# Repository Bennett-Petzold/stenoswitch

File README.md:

Split stenography keyboard supporting USB, Bluetooth, battery, and embedded Plover translation.

# Warning!!!
There is no warranty, implied or otherwise, on this repository!
This is a hobby project by someone who has no formal education or training in PCB design. 
I _CANNOT_ guarantee that the battery circuit is safe.
I _CANNOT_ guarantee bluetooth communications comply with safety regulations.
I _AM NOT_ liable if you make this project and it is dysfunctional.
Understand that there is a risk of electrical fire due to the lithium ion battery.
Understand that wireless communications are untested and may interfere with pacemakers etc.

# Capabilities
TODO.

# Licenses
All code is licensed under the Mozilla Public License 2.0.
All non-code is licensed under CC BY-SA 4.0.
Both licenses allow for commercial use, but any commercial modification must be licensed under the same terms.
They will not "infect" other proprietary works.

# Subfolders
Each subfolder 

## Assembling the Project
See [assembly/README.md](assembly/README.md).

## PCB
KiCAD designs for printed circuit board.
See [pcb/README.md](pcb/README.md) for more.

## Software
Hardware-independent software built into the machine image.
Specialization to a specific hardware is handled in yocto.
See [software/README.md](software/README.md).

## Yocto Image
This defines the machine-specific image.
See [yocto/README.md](yocto/README.md).

# Releases
Some release resources are manually uploaded.
The initial install is done with the full disk image.
Subsequent updates are done by flashing ONLY the length of the full disk image.

# Appendix

### Steno Resources
* https://www.openstenoproject.org/plover/
* https://plover.wiki/index.php/Plover_Wiki
* https://lapwing.aerick.ca/
* https://www.artofchording.com/
* https://www.openstenoproject.org/learn-plover/home.html

### Approximate Cost
These are based on my costs (including shipping and taxes) September 2025, US address.
* $35 for keyswitches and lube
* $18 for springs
* $12 for battery
* $17 for Raspberry Pi
* $60 for components from DigiKey
* $50 for 5 PCBs both sides, 1 stencil from JLCPCB
Expect ~ $200 for a full single order.
There are electronics and buying in bulk reduces per-board prices.
Shipping is also a significant part of the price in these low quantities.

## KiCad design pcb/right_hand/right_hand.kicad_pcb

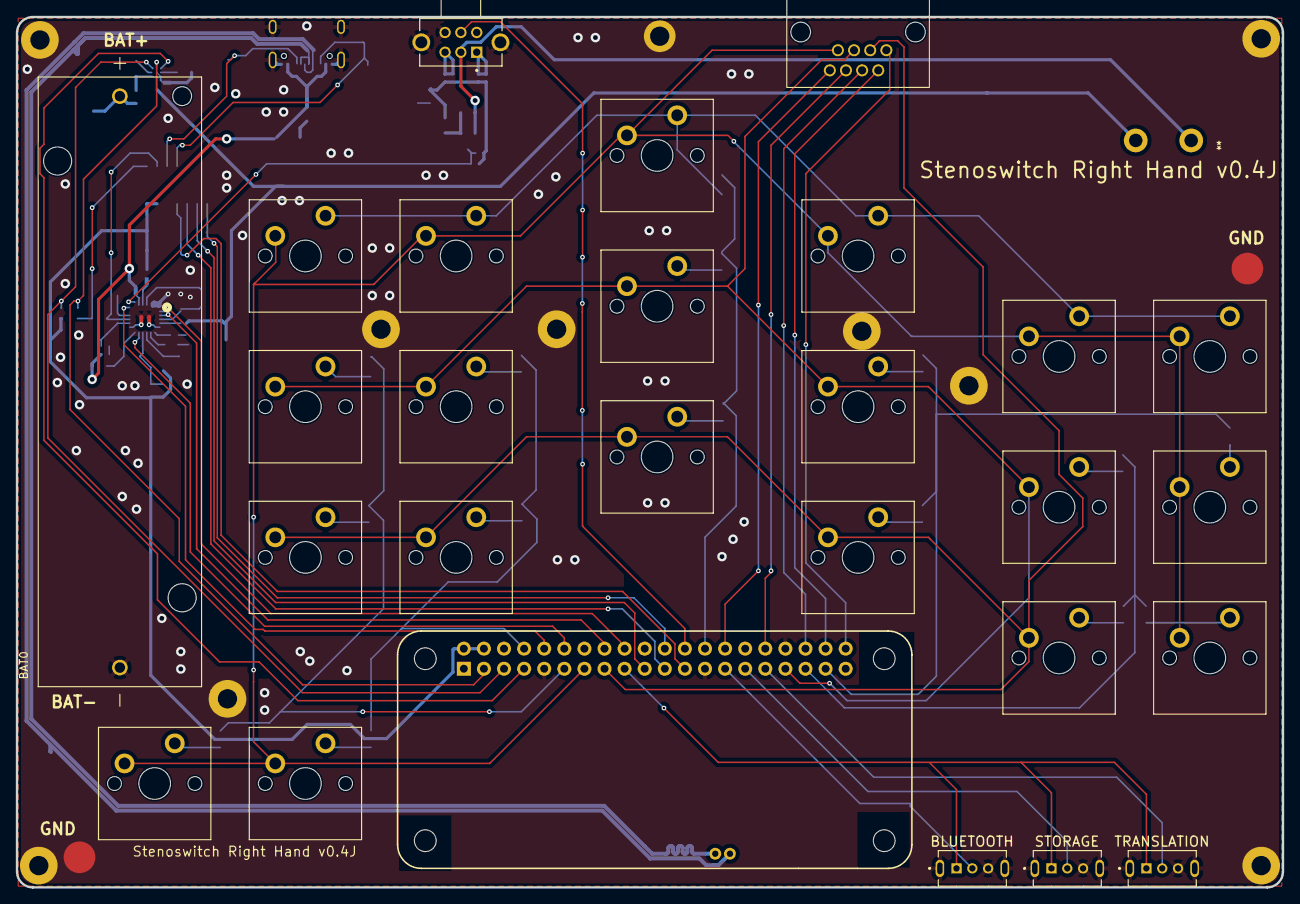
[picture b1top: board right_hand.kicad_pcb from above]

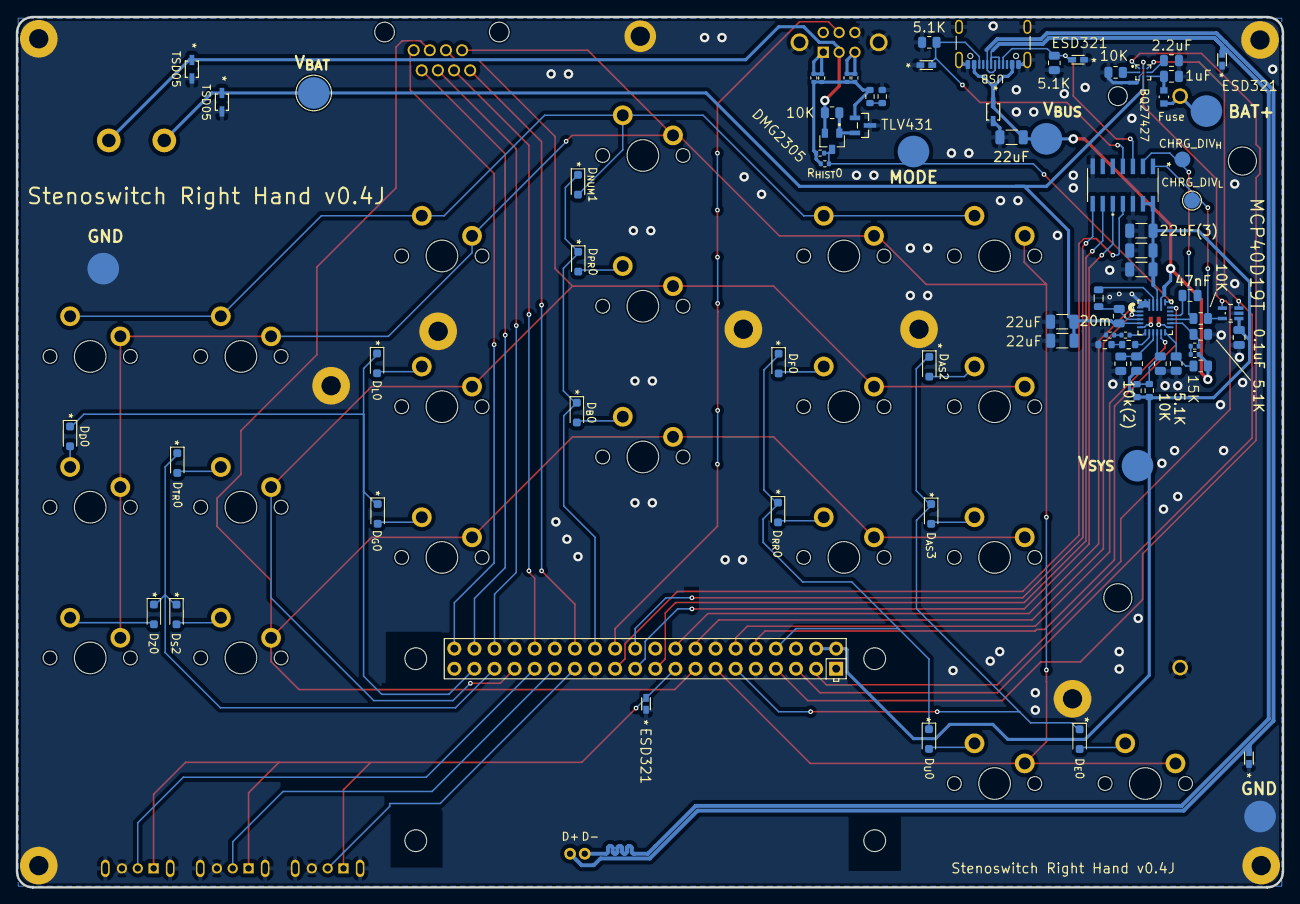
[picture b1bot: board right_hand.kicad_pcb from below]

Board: 2 copper layers, 160.0 x 110.0 mm, 104 parts (75 on the bottom side), 82 nets.

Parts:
A1: Raspberry Pi Zero v1.3; RASPI_ZERO_FULL
Asterisk2, Asterisk3: SW_Push; SW_Cherry_MX_PCB
B0: SW_Push; SW_Cherry_MX_PCB
BAT0: 1043; BAT_1043
BAT_Decouple0: 1uF; C_0805_2012Metric
BAT_EN0: RA1H1C112R; SW_RA1H1C112R_EWI
BAT_Fuse0: 2.5 A; FUSE_ERBRE_PAN
BAT_MIN0: DMG2305UX-7; SOT91P240X110-3N_DMG2305UX-7
BIN_Pulldown0: 10K; R_0805_2012Metric
BLUETOOTH0: SLW-864587-2A-RA-N-D; SW_SLW-864587-2A-RA-N-D
Battery_Charger0: MP2637GR-P; QFN-24_MP2637_MNP
Battery_Monitor0: BQ27427YZFR; IC_BQ27427YZFR
CHRG_Bypass0: 2.2uH; L_0805_2012Metric
CHRG_DIV_{L}: TestPoint_Pad_D2.0mm
CHRG_Decouple0: 47nF; C_0805_2012Metric
CHRG_Shunt0: 20m; R_0805_2012Metric
CR0, CR1, CR3, CR4, CR5: ESD321DYAR; SOT5x3_DYA_TEX
CR2, CR6, CR7: TSD05DYFR; TVS_SOD2_DYF_TEX
C_{BATT}0, C_{BATT}1: 22uF; C_1206_3216Metric
C_{SYS}0, C_{SYS}1, C_{SYS}2: 22uF; C_1206_3216Metric
Current_Monitor1: MCP3204T-CI/SL; SOIC14-N_MC_MCH
D0: SW_Push; SW_Cherry_MX_PCB
D_{AS}2, D_{AS}3: 1N4148WX-TP; D_SOD-323_HandSoldering
D_{B}0: 1N4148WX-TP; D_SOD-323_HandSoldering
D_{D}0: 1N4148WX-TP; D_SOD-323_HandSoldering
D_{E}0: 1N4148WX-TP; D_SOD-323_HandSoldering
D_{F}0: 1N4148WX-TP; D_SOD-323_HandSoldering
D_{G}0: 1N4148WX-TP; D_SOD-323_HandSoldering
D_{L}0: 1N4148WX-TP; D_SOD-323_HandSoldering
D_{NUM}1: 1N4148WX-TP; D_SOD-323_HandSoldering
D_{PR}0: 1N4148WX-TP; D_SOD-323_HandSoldering
D_{RR}0: 1N4148WX-TP; D_SOD-323_HandSoldering
D_{S}2: 1N4148WX-TP; D_SOD-323_HandSoldering
D_{TR}0: 1N4148WX-TP; D_SOD-323_HandSoldering
D_{U}0: 1N4148WX-TP; D_SOD-323_HandSoldering
D_{Z}0: 1N4148WX-TP; D_SOD-323_HandSoldering
E0: SW_Push; SW_Cherry_MX_PCB
F0: SW_Push; SW_Cherry_MX_PCB
G0: SW_Push; SW_Cherry_MX_PCB
L0: SW_Push; SW_Cherry_MX_PCB
NT0, NT1, NT2, NT3, NT4: NetTie_2; NetTie-2_SMD_Pad0.5mm
Number_Bar6, Number_Bar7, Number_Bar8, Number_Bar9, Number_Bar10, Number_Bar11: SW_Push; SW_Cherry_MX_PCB
P_{R}0: SW_Push; SW_Cherry_MX_PCB
RFB_{H}0: 33K; R_0603_1608Metric
RFB_{H}1: 750K; R_0603_1608Metric
RFB_{L}0: 10K; R_0805_2012Metric
RLIM_Decouple0: 0.1uF; C_0805_2012Metric
RLIM_{H}0: 10K; R_0805_2012Metric
RLIM_{L}0: MCP40D19T-104E_LT; SOT65P210X110-5N
RNTC_{H}0: 10K; R_0805_2012Metric
RNTC_{L}0: 10K; R_0805_2012Metric
RREG_{H}0: 15K; R_0805_2012Metric
RREG_{L}0: 5.1K; R_0805_2012Metric
RWIN_{H}0: 20K; R_0402_1005Metric
RWIN_{H}1: 1.5K; R_0402_1005Metric
RWIN_{L}0: 5.1K; R_0805_2012Metric
R_{HIST}0, R_{HIST}1: 1M; R_0402_1005Metric
R_{ISET}0: 40.2K; R_0603_1608Metric
R_{ISET}1: 33K; R_0603_1608Metric
R_{Lower}0: 3.9K; R_0603_1608Metric
R_{Lower}1: 120; R_0603_1608Metric
R_{OLIM}0: 470K; R_0402_1005Metric
R_{OLIM}1: 120K; R_0402_1005Metric
R_{Pullup}0: 10K; R_0805_2012Metric
R_{R}0: SW_Push; SW_Cherry_MX_PCB
R_{Store}0: 470K; R_0402_1005Metric
R_{Store}1: 8.2K; R_0402_1005Metric
R_{Upper}0: 56K; R_0402_1005Metric
R_{Upper}1: 8.2K; R_0402_1005Metric
Right_Plug0: RJ45; 8P8C_942
S2: SW_Push; SW_Cherry_MX_PCB
STORAGE0: SLW-864587-2A-RA-N-D; SW_SLW-864587-2A-RA-N-D
STORE_EN0: EG2208; SW_EG2208
TRANSLATION0: SLW-864587-2A-RA-N-D; SW_SLW-864587-2A-RA-N-D
T_{R}0: SW_Push; SW_Cherry_MX_PCB
U0: SW_Push; SW_Cherry_MX_PCB
USB0: USB4105-GF-A; USB_C_Receptacle_GCT_USB4105-xx-A_16P_TopMnt_Horizontal
USB_Default_Power_CC1, USB_Default_Power_CC2: 5.1K; R_0805_2012Metric
VBAT_PASS0: TLV431BIDBZR; DBZ3
VBUS_Bypass0: 22uF; C_1206_3216Metric
VDD_Decouple0: 2.2uF; C_0805_2012Metric
Z0: SW_Push; SW_Cherry_MX_PCB

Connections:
/Control/ALERT_{BATMON}: A1.7 (GP4), Battery_Monitor0.A1 (GPOUT)
/Control/BAT_{ON}: A1.16 (GP23), Battery_Charger0.3 (*BOOST)
/Control/CHG_{EN}: A1.10 (GP15/RXD), Battery_Charger0.18 (EN)
/Control/CHG_{ON}: A1.18 (GP24), Battery_Charger0.2 (*CHG)
/Control/CLK_{CURRENT}: A1.23 (GP11/SCLK), Current_Monitor1.11 (CLK)
/Control/CS_{CURRENT}: A1.22 (GP25), Current_Monitor1.8 (*CS/SHDN)
/Control/DIN_{CURRENT}: A1.19 (GP10/MOSI), Current_Monitor1.9 (DIN)
/Control/DOUT_{CURRENT}: A1.21 (GP9/MISO), Current_Monitor1.10 (DOUT)
/Control/Data_N: A1.PP23 (USB_D-), CR0.1, USB0.A7 (D-), USB0.B7 (D-)
/Control/Data_P: A1.PP22 (USB_D+), CR1.1, USB0.A6 (D+), USB0.B6 (D+)
/Control/Right_Columns0: A1.35 (GP19), D_{S}2.1 (K), D_{TR}0.1 (K), D_{Z}0.1 (K)
/Control/Right_Columns1: A1.37 (GP26), D_{D}0.1 (K), D_{G}0.1 (K), D_{L}0.1 (K)
/Control/Right_Columns2: A1.26 (GP7/CS1), D_{B}0.1 (K), D_{NUM}1.1 (K), D_{PR}0.1 (K)
/Control/Right_Columns3: A1.8 (GP14/TXD), D_{F}0.1 (K), D_{RR}0.1 (K), D_{U}0.1 (K)
/Control/Right_Columns4: A1.11 (GP17), D_{AS}2.1 (K), D_{AS}3.1 (K), D_{E}0.1 (K)
/Control/SCL: A1.5 (GP3/SCL), Battery_Monitor0.A3 (SCL), RLIM_{L}0.3 (SCL)
/Control/SDA: A1.3 (GP2/SDA), Battery_Monitor0.A2 (SDA), RLIM_{L}0.4 (SDA)
/Control/STORE_{ON}: A1.24 (GP8/CS0), STORE_EN0.5
/Control/USB_{ON}: A1.12 (GP18), Battery_Charger0.11 (*ACOK)
/Control/V_{SYS}: A1.2 (+5V), A1.4 (+5V), C_{SYS}0.1, C_{SYS}1.1, C_{SYS}2.1, Current_Monitor1.13 (VREF), Current_Monitor1.14 (VDD), NT0.1, RFB_{H}0.2, RFB_{H}1.2, RLIM_Decouple0.1, RLIM_{L}0.1 (VDD), RNTC_{H}0.1
/Interface/Battery/CHRG_DIV_{H}: Battery_Charger0.15 (ILIM), Current_Monitor1.2 (CH1), RLIM_{H}0.1
/Interface/Battery/CHRG_DIV_{L}: CHRG_DIV_{L}.1, Current_Monitor1.1 (CH0), RLIM_{H}0.2, RLIM_{L}0.5 (W)
/Interface/Battery/V_{BUS}: CR2.1 (I/O), NT1.2, RREG_{H}0.1, RWIN_{H}0.1, USB0.A4 (VBUS), USB0.A9 (VBUS), USB0.B4 (VBUS), USB0.B9 (VBUS), VBUS_Bypass0.1
/Left_Columns0: A1.28 (GP1), Right_Plug0.4
/Left_Columns1: A1.32 (GP12/PWM0), Right_Plug0.3
/Left_Columns2: A1.36 (GP16), Right_Plug0.2
/Left_Columns3: A1.38 (GP20), Right_Plug0.1
/Left_Columns4: A1.40 (GP21), Right_Plug0.5
/Rows0: A1.33 (GP13/PWM1), Asterisk2.1, F0.1, L0.1, P_{R}0.1, Right_Plug0.7, T_{R}0.1
/Rows1: A1.15 (GP22), Asterisk3.1, B0.1, G0.1, R_{R}0.1, Right_Plug0.6, S2.1
/Rows2: A1.13 (GP27), D0.1, E0.1, Number_Bar6.1, Number_Bar7.1, Number_Bar8.1, Number_Bar9.1, Number_Bar10.1, Number_Bar11.1, Right_Plug0.8, U0.1, Z0.1
GND: A1.9 (GND), A1.14 (GND), A1.25 (GND), A1.30 (GND), A1.34 (GND), BAT0.N, BAT_Decouple0.2, BIN_Pulldown0.1, BLUETOOTH0.3, BLUETOOTH0.SH1, BLUETOOTH0.SH2, Battery_Charger0.1 (PGND), Battery_Charger0.23 (PGND), Battery_Charger0.24 (PGND), CHRG_Decouple0.2, CR0.2, CR1.2, CR2.2 (GND), CR3.2, CR4.2, CR5.2, CR6.2 (GND), CR7.2 (GND), C_{BATT}0.2, C_{BATT}1.2, C_{SYS}0.2, C_{SYS}1.2, C_{SYS}2.2, Current_Monitor1.7 (DGND), Current_Monitor1.12 (AGND), NT2.1, NT3.2, NT4.2, RFB_{L}0.1, RLIM_Decouple0.2, RLIM_{L}0.2 (VSS), RNTC_{L}0.2, RREG_{L}0.2, RWIN_{L}0.2, R_{ISET}1.2, R_{Lower}1.2, R_{OLIM}1.2, STORAGE0.3, STORAGE0.SH1, STORAGE0.SH2, STORE_EN0.6, STORE_EN0.S1, STORE_EN0.S2, TRANSLATION0.3, TRANSLATION0.SH1, TRANSLATION0.SH2, USB0.A1 (GND), USB0.A12 (GND), USB0.B1 (GND), USB0.B12 (GND), USB0.S1 (SHIELD), USB_Default_Power_CC1.2, USB_Default_Power_CC2.2, VBAT_PASS0.3 (ANODE), VBUS_Bypass0.2, VDD_Decouple0.2
unnamed: A1.17 (+3V3), BLUETOOTH0.1, CR5.1, STORAGE0.1, TRANSLATION0.1
unnamed: A1.27 (GP0), BLUETOOTH0.2
unnamed: A1.29 (GP5), STORAGE0.2
unnamed: A1.31 (GP6), TRANSLATION0.2
unnamed: BAT0.P, BAT_Fuse0.2
unnamed: Battery_Charger0.6 (AGND), NT4.1
unnamed: BAT_EN0.2, Battery_Charger0.5 (BATT), Battery_Monitor0.C2 (SRX), CHRG_Shunt0.1, CR6.1 (I/O), C_{BATT}0.1, C_{BATT}1.1
unnamed: Battery_Charger0.4 (CSP), CHRG_Bypass0.1, CHRG_Shunt0.2
unnamed: Battery_Charger0.10 (FB), RFB_{H}0.1, RFB_{H}1.1, RFB_{L}0.2
unnamed: Battery_Charger0.8 (ISET), R_{ISET}0.1
unnamed: BAT_MIN0.3, Battery_Charger0.19 (MODE), R_{HIST}0.1, R_{HIST}1.1
unnamed: Battery_Charger0.9 (NTC), RNTC_{H}0.2, RNTC_{L}0.1
unnamed: Battery_Charger0.7 (OLIM), R_{OLIM}0.1
unnamed: Battery_Charger0.14 (PWIN), RWIN_{H}1.2, RWIN_{L}0.1
unnamed: Battery_Charger0.12 (REG), RREG_{H}0.2, RREG_{L}0.1
unnamed: Battery_Charger0.22 (SW), CHRG_Bypass0.2
unnamed: Battery_Charger0.21 (SYS), NT0.2
unnamed: Battery_Charger0.13 (TMR), NT3.1
unnamed: Battery_Charger0.16 (VCC), CHRG_Decouple0.1
unnamed: Battery_Charger0.20 (VIN), NT1.1
unnamed: BAT_Decouple0.1, BAT_Fuse0.1, Battery_Monitor0.C3 (BAT)
unnamed: BIN_Pulldown0.2, Battery_Monitor0.B1 (BIN)
unnamed: Battery_Monitor0.B3 (VDD), VDD_Decouple0.1
unnamed: Battery_Monitor0.B2 (VSS), Battery_Monitor0.C1 (VSS__1), NT2.2
unnamed: BAT_EN0.1, BAT_MIN0.2, CR7.1 (I/O), R_{Pullup}0.1, STORE_EN0.2, STORE_EN0.4
unnamed: CR3.1, Current_Monitor1.3 (CH2), USB0.B5 (CC2), USB_Default_Power_CC2.1
unnamed: CR4.1, Current_Monitor1.4 (CH3), USB0.A5 (CC1), USB_Default_Power_CC1.1
unnamed: Asterisk2.2, D_{AS}2.2 (A)
unnamed: Asterisk3.2, D_{AS}3.2 (A)
unnamed: B0.2, D_{B}0.2 (A)
unnamed: D0.2, D_{D}0.2 (A)
unnamed: D_{E}0.2 (A), E0.2
unnamed: D_{F}0.2 (A), F0.2
unnamed: D_{G}0.2 (A), G0.2
unnamed: D_{L}0.2 (A), L0.2
unnamed: D_{NUM}1.2 (A), Number_Bar6.2, Number_Bar7.2, Number_Bar8.2, Number_Bar9.2, Number_Bar10.2, Number_Bar11.2
unnamed: D_{PR}0.2 (A), P_{R}0.2
unnamed: D_{RR}0.2 (A), R_{R}0.2
unnamed: D_{S}2.2 (A), S2.2
unnamed: D_{TR}0.2 (A), T_{R}0.2
unnamed: D_{U}0.2 (A), U0.2
unnamed: D_{Z}0.2 (A), Z0.2
unnamed: RWIN_{H}0.2, RWIN_{H}1.1
unnamed: R_{ISET}0.2, R_{ISET}1.1
unnamed: R_{Lower}0.2, R_{Lower}1.1
unnamed: R_{OLIM}0.2, R_{OLIM}1.1
unnamed: R_{Store}0.1, R_{Store}1.1, STORE_EN0.1
unnamed: R_{Upper}0.1, R_{Upper}1.1, STORE_EN0.3
unnamed: BAT_MIN0.1, R_{Pullup}0.2, VBAT_PASS0.2 (CATHODE)
unnamed: R_{HIST}0.2, R_{HIST}1.2, R_{Lower}0.1, R_{Store}0.2, R_{Store}1.2, R_{Upper}0.2, R_{Upper}1.2, VBAT_PASS0.1 (REF)

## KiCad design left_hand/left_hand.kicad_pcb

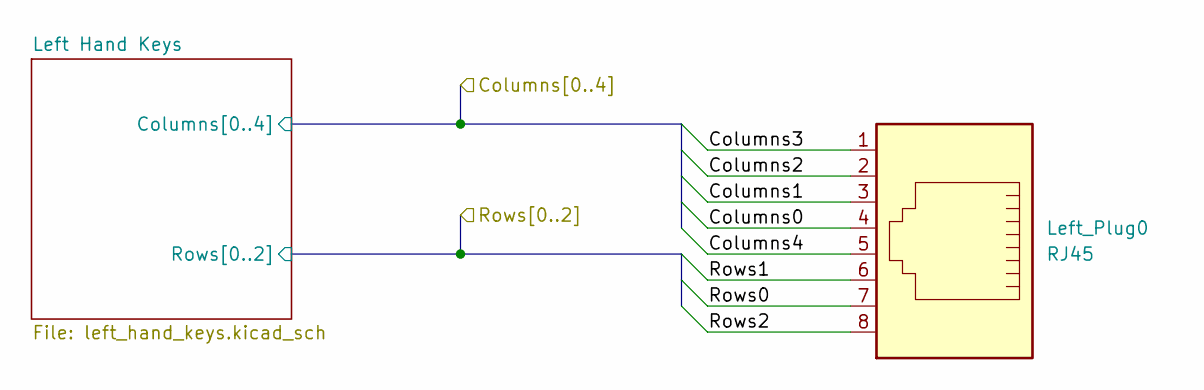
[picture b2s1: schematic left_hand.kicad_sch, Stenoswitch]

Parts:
Left_Plug0: RJ45; 8P8C_942

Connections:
/Columns0: Left_Plug0.4; also elsewhere on the board
/Columns1: Left_Plug0.3; also elsewhere on the board
/Columns2: Left_Plug0.2; also elsewhere on the board
/Columns3: Left_Plug0.1; also elsewhere on the board
/Columns4: Left_Plug0.5; also elsewhere on the board
/Rows0: Left_Plug0.7; also elsewhere on the board
/Rows1: Left_Plug0.6; also elsewhere on the board
/Rows2: Left_Plug0.8; also elsewhere on the board

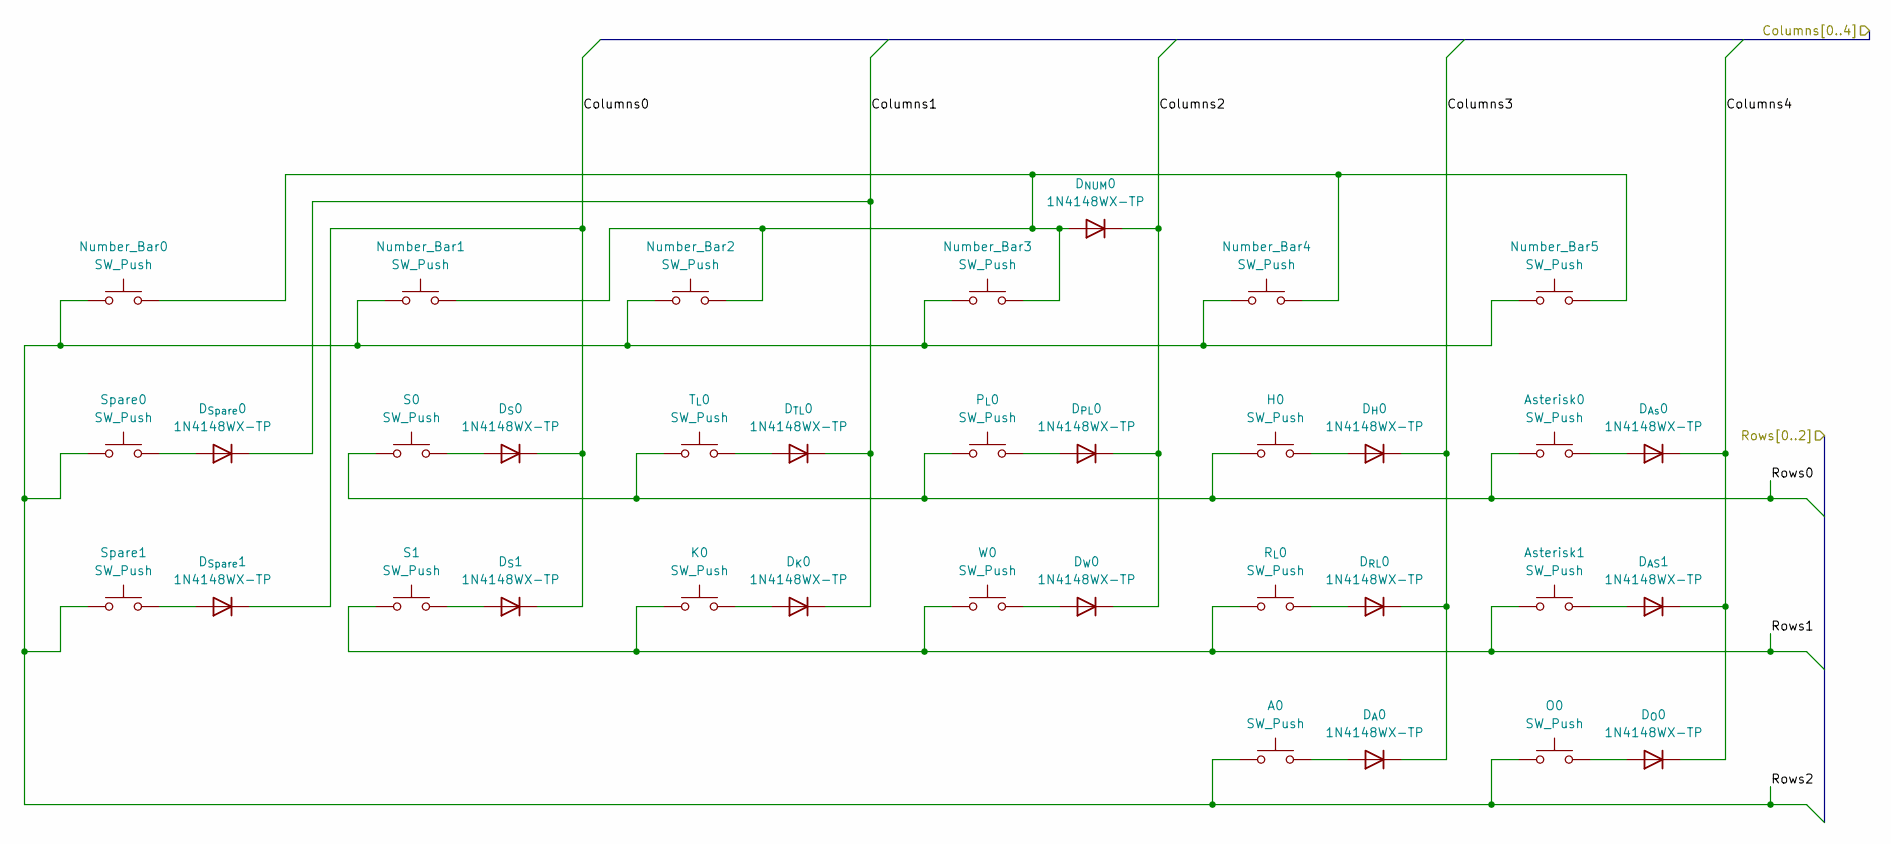
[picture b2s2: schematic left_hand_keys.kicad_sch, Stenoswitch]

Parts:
A0: SW_Push; SW_Cherry_MX_PCB
Asterisk0, Asterisk1: SW_Push; SW_Cherry_MX_PCB
D_{AS}1: 1N4148WX-TP; D_SOD-323
D_{As}0: 1N4148WX-TP; D_SOD-323
D_{A}0: 1N4148WX-TP; D_SOD-323
D_{H}0: 1N4148WX-TP; D_SOD-323
D_{K}0: 1N4148WX-TP; D_SOD-323
D_{NUM}0: 1N4148WX-TP; D_SOD-323
D_{O}0: 1N4148WX-TP; D_SOD-323
D_{PL}0: 1N4148WX-TP; D_SOD-323
D_{RL}0: 1N4148WX-TP; D_SOD-323
D_{Spare}0, D_{Spare}1: 1N4148WX-TP; D_SOD-323
D_{S}0, D_{S}1: 1N4148WX-TP; D_SOD-323
D_{TL}0: 1N4148WX-TP; D_SOD-323
D_{W}0: 1N4148WX-TP; D_SOD-323
H0: SW_Push; SW_Cherry_MX_PCB
K0: SW_Push; SW_Cherry_MX_PCB
Number_Bar0, Number_Bar1, Number_Bar2, Number_Bar3, Number_Bar4, Number_Bar5: SW_Push; SW_Cherry_MX_PCB
O0: SW_Push; SW_Cherry_MX_PCB
P_{L}0: SW_Push; SW_Cherry_MX_PCB
R_{L}0: SW_Push; SW_Cherry_MX_PCB
S0, S1: SW_Push; SW_Cherry_MX_PCB
Spare0, Spare1: SW_Push; SW_Cherry_MX_PCB
T_{L}0: SW_Push; SW_Cherry_MX_PCB
W0: SW_Push; SW_Cherry_MX_PCB

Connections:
/Columns0: D_{Spare}1.1 (K), D_{S}0.1 (K), D_{S}1.1 (K); also elsewhere on the board
/Columns1: D_{K}0.1 (K), D_{Spare}0.1 (K), D_{TL}0.1 (K); also elsewhere on the board
/Columns2: D_{NUM}0.1 (K), D_{PL}0.1 (K), D_{W}0.1 (K); also elsewhere on the board
/Columns3: D_{A}0.1 (K), D_{H}0.1 (K), D_{RL}0.1 (K); also elsewhere on the board
/Columns4: D_{AS}1.1 (K), D_{As}0.1 (K), D_{O}0.1 (K); also elsewhere on the board
/Rows0: Asterisk0.1, H0.1, P_{L}0.1, S0.1, T_{L}0.1; also elsewhere on the board
/Rows1: Asterisk1.1, K0.1, R_{L}0.1, S1.1, W0.1; also elsewhere on the board
/Rows2: A0.1, Number_Bar0.1, Number_Bar1.1, Number_Bar2.1, Number_Bar3.1, Number_Bar4.1, Number_Bar5.1, O0.1, Spare0.1, Spare1.1; also elsewhere on the board
unnamed: Asterisk1.2, D_{AS}1.2 (A)
unnamed: Asterisk0.2, D_{As}0.2 (A)
unnamed: A0.2, D_{A}0.2 (A)
unnamed: D_{H}0.2 (A), H0.2
unnamed: D_{K}0.2 (A), K0.2
unnamed: D_{NUM}0.2 (A), Number_Bar0.2, Number_Bar1.2, Number_Bar2.2, Number_Bar3.2, Number_Bar4.2, Number_Bar5.2
unnamed: D_{O}0.2 (A), O0.2
unnamed: D_{PL}0.2 (A), P_{L}0.2
unnamed: D_{RL}0.2 (A), R_{L}0.2
unnamed: D_{Spare}0.2 (A), Spare0.2
unnamed: D_{Spare}1.2 (A), Spare1.2
unnamed: D_{S}0.2 (A), S0.2
unnamed: D_{S}1.2 (A), S1.2
unnamed: D_{TL}0.2 (A), T_{L}0.2
unnamed: D_{W}0.2 (A), W0.2

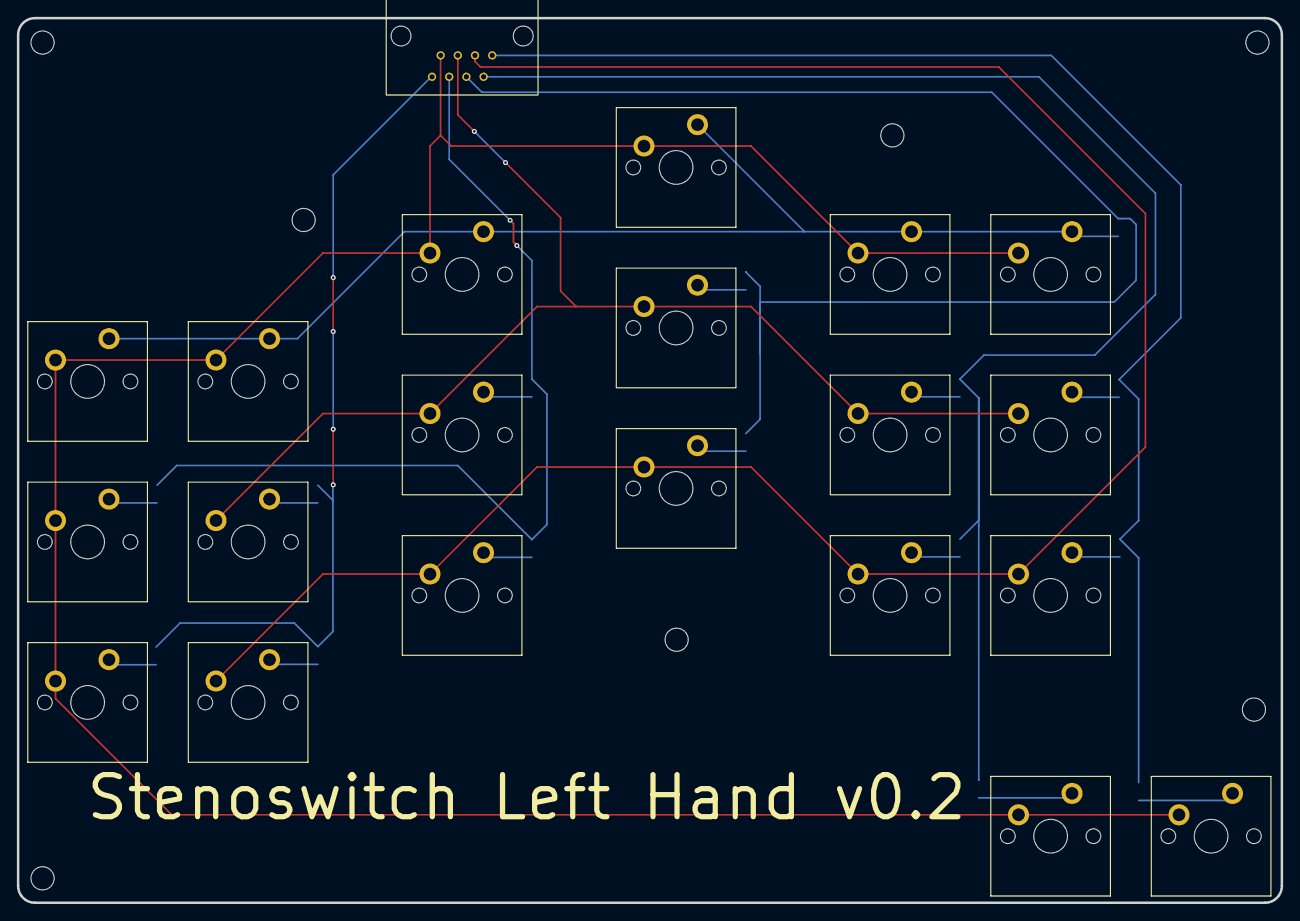
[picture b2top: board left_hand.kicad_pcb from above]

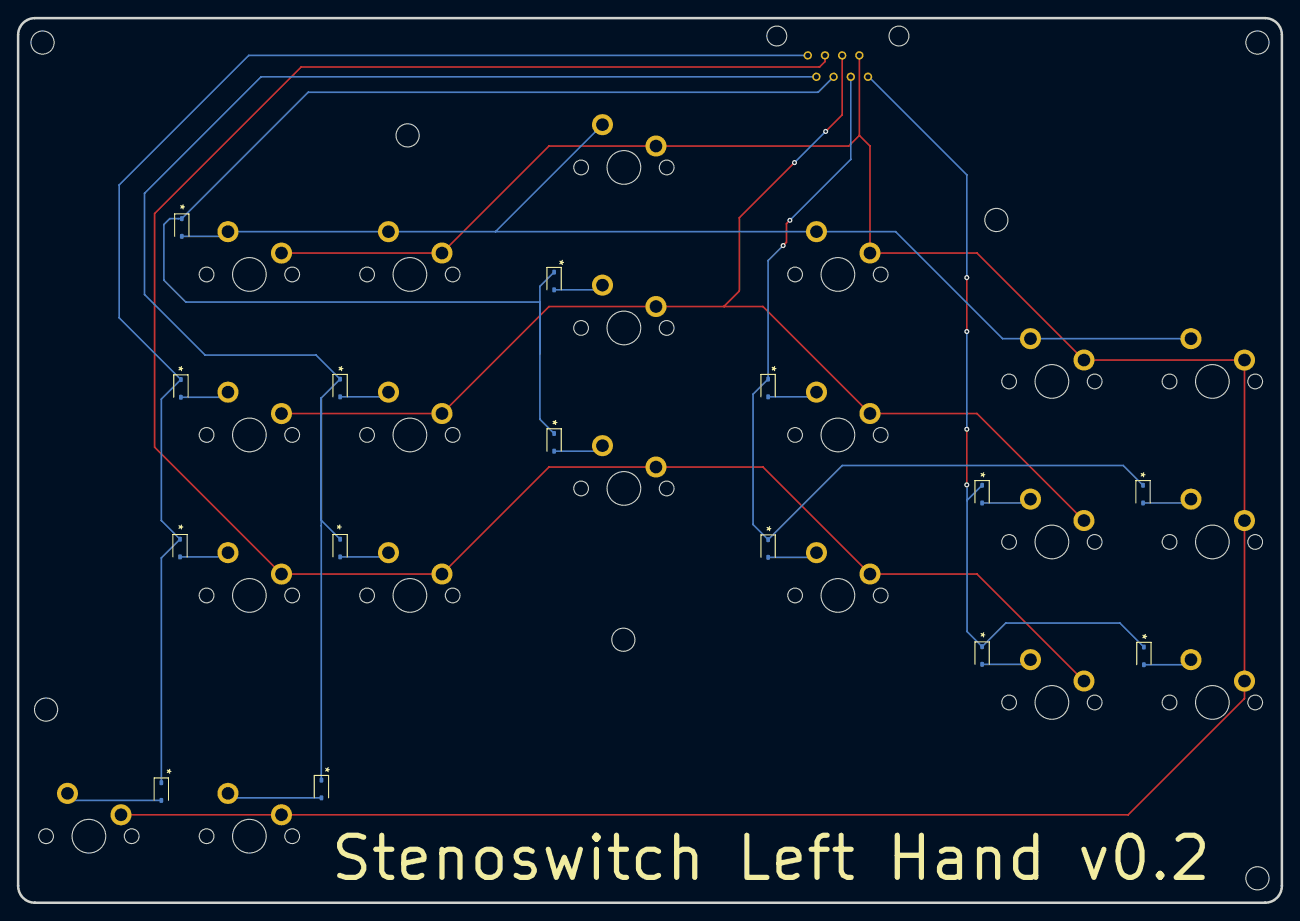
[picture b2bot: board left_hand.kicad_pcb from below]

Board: 2 copper layers, 150.0 x 105.0 mm, 36 parts (15 on the bottom side), 23 nets.

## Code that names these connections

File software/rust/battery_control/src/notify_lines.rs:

use std::sync::mpsc;

use gpio_cdev::{Chip, EventRequestFlags, EventType, LineRequestFlags};
use log::debug;

const BATMON_LINE: &str = if let Some(x) = option_env!("ALERT_BATMON") {
    x
} else {
    "NaN"
};
const CHG_ON_LINE: &str = if let Some(x) = option_env!("CHG_ON") {
    x
} else {
    "NaN "
};
const USB_ON_LINE: &str = if let Some(x) = option_env!("USB_ON") {
    x
} else {
    "NaN "
};
const BAT_ON_LINE: &str = if let Some(x) = option_env!("BAT_ON") {
    x
} else {
    "NaN "
};
const STORE_ON_LINE: &str = if let Some(x) = option_env!("STORE_ON") {
    x
} else {
    "NaN "
};

#[derive(Debug, Clone, Copy, PartialEq, Eq, PartialOrd, Ord, Hash)]
pub enum NotifySource {
    Batmon,
    ChgOn,
    UsbOn,
    BatOn,
    StoreOn,
}

#[derive(Debug, Clone, Copy, PartialEq, Eq, PartialOrd, Ord, Hash)]
pub struct LineNotification {
    pub source: NotifySource,
    pub value: bool,
}

pub struct NotifyLines {
    notifications: mpsc::Receiver<LineNotification>,
}

impl NotifyLines {
    /// Creates a line monitor, panicking on hardware failures.
    pub fn new() -> Self {
        let (tx, rx) = mpsc::sync_channel(0);

        let mut chip = Chip::new(option_env!("GPIO_CHIP").unwrap_or("/dev/null")).unwrap();

        let _both_edges = [
            (CHG_ON_LINE, NotifySource::ChgOn),
            (USB_ON_LINE, NotifySource::UsbOn),
            (BAT_ON_LINE, NotifySource::BatOn),
            (STORE_ON_LINE, NotifySource::StoreOn),
        ]
        .map(|(line, source)| {
            let tx = tx.clone();
            let line = chip.get_line(str::parse(line).unwrap()).unwrap();
            std::thread::spawn(move || {
                let events = line
                    .events(
                        LineRequestFlags::INPUT.union(LineRequestFlags::BIAS_PULL_UP),
                        EventRequestFlags::BOTH_EDGES,
                        &format!("battery_control {:?}", source),
                    )
                    .unwrap();

                let init_value = events.get_value().unwrap() != 0;
                tx.send(LineNotification {
                    source,
                    value: init_value,
                })
                .unwrap();

                for event in events {
                    let value = match event.unwrap().event_type() {
                        EventType::RisingEdge => true,
                        EventType::FallingEdge => false,
                    };
                    debug!("Line event: {source:#?} -> {value}");
                    tx.send(LineNotification { source, value }).unwrap();
                }
            })
        });

        let _batmon = {
            let line = chip.get_line(str::parse(BATMON_LINE).unwrap()).unwrap();
            std::thread::spawn(move || {
                let events = line
                    .events(
                        LineRequestFlags::INPUT.union(LineRequestFlags::BIAS_PULL_UP),
                        EventRequestFlags::FALLING_EDGE,
                        "battery_control BATMON",
                    )
                    .unwrap();

                let init_value = events.get_value().unwrap() != 0;
                tx.send(LineNotification {
                    source: NotifySource::Batmon,
                    value: init_value,
                })
                .unwrap();

                for _event in events {
                    debug!("Line event: {:#?} -> {}", NotifySource::Batmon, false);
                    tx.send(LineNotification {
                        source: NotifySource::Batmon,
                        value: false,
                    })
                    .unwrap();
                }
            })
        };

        Self { notifications: rx }
    }

    /// Blocks until a new notification, then returns that event.
    pub fn next_notification(&self) -> LineNotification {
        let notification = self.notifications.recv().unwrap();
        debug!(
            "Recv line event: {:#?} -> {}",
            notification.source, notification.value
        );
        notification
    }
}

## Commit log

2025-07-25 Add libraries
2025-07-30 Core PCB Layout, Incl Key Matrices
2025-07-30 Label keys
2025-08-04 Design power
2025-08-06 Adjust battery resistor values
2025-08-06 Add custom 942 footprint
2025-08-07 Remove unnecessary diodes
2025-08-08 Rework battery entirely
2025-08-09 Assign footprints
2025-08-09 Init right and left PCBs
2025-08-09 Rename keyswitch diodes
2025-08-09 Layout left hand side
2025-08-09 Standardize connector names
2025-08-09 Generate left hand vias
2025-08-09 Match left hand pins
2025-08-09 Make battery holder thru-hole
2025-08-10 Assign models for right hand
2025-08-10 Put connector on front
2025-08-10 Size up components
2025-08-10 Place right hand keys
2025-08-25 Complete most of RHS layout
2025-08-30 Rework left hand
2025-08-30 Rework right hand
2025-08-30 Replace USB connector
2025-08-30 Add JLCPCB rules
2025-08-30 Add labeling
2025-09-05 Update libraries
2025-09-05 Update layout
2025-09-05 Add holes to stencil
2025-09-05 Plot according to JLC rules
2025-09-05 Rename core files
2025-09-06 Add parts list
2025-09-06 Make PCB subdirectory
2025-09-07 Add license
2025-09-07 Init software
2025-09-07 Establish core yocto build
2025-09-07 Create README file and assembly dir
2025-09-15 Move rust to subdir
2025-09-16 Generate wifi-debuggable image
2025-09-19 Add prototype keycap
2025-09-27 Keyboard scanning skeleton
2025-09-27 Fix gitignores
2025-09-27 Use gitignore in rust recipe
2025-10-06 Add 3D printed fixtures
2025-10-21 Make left hand pads larger
2025-10-21 Plate right hand mounting holes
2025-10-21 Fix Bluetooh Enable positioning
2025-10-21 Make right hand pads larger
2025-10-21 Right hand DRC check fixes
2025-10-21 Left hand plate mounting holes
2025-10-21 Rework footprints
2025-10-21 Change ESD layout
2025-10-21 Enlarge VSYS TVS footprint
2025-10-21 Extra right hand tweaks and cleanup
2025-10-21 Update right hand metadata
2025-10-21 Readjust positive data ESD
2025-10-21 Add more ESD protection
2025-10-21 Connect right_columns 2 to RPi
2025-10-21 Add paste to USB-C shield
2025-10-21 Ground right hand through holes
2025-10-21 Move toggle switches closer together
2025-10-21 Extra copper
2025-10-21 Plate left hand through holes
2025-10-23 Update parts counts
2025-10-25 Add pypy to replace python
2025-10-26 Implement core of current monitoring
2025-10-26 Core of full battery control
2025-10-29 Change from 2KHz to 2MHz
2025-10-29 Pypy tweaks and disable
2025-10-29 Add autoexpand to fstab vfat
2025-10-29 Debug logging for systemd
2025-10-29 Add Rust env variables
2025-10-30 Remove separate spi chip select; separate rheostat i2c
2025-10-30 Replace env with option_env
2025-10-30 Add StoreOn line
2025-10-30 Run clippy
2025-10-31 SPI pin full tweaks
2025-11-02 Fix SPI overlay to use built in
2025-11-02 Create systemd services for stenoswitch rust code
2025-11-02 Shrink boot partition
2025-11-02 Add pin monitor functions
2025-11-02 Fully define raspberry pi overlay config
2025-11-02 Create user partition automatically
2025-11-02 Fix waiting logic
2025-11-02 Just get_value from events
2025-11-02 Make fstab automount
2025-11-02 Create a dummy USB service
    Also throw in a bluetooth stub.
2025-11-02 Change from notify to simple
2025-11-02 Flip timing math
2025-11-03 Partial work to add Plover
2025-11-03 Create non-hanging fstab
2025-11-03 Add script to help with sd card flashing
2025-11-04 Add plover
2025-11-04 Clean up extra layers
2025-11-04 Enable USB gadget
2025-11-04 Add udc status debug print
2025-11-04 Clean up plover autogenerated deps
2025-11-04 Use noui service installation
2025-11-04 Remove gui references
2025-11-04 Create plover config by default
2025-11-04 Set dwc to peripheral
2025-11-04 Get rid of overlay dir
2025-11-09 Add software i2c
2025-11-09 Use software i2c
2025-11-10 Flesh out all critical battery control
2025-11-10 Only update min stat while discharging
2025-11-10 Update filesystem defs for software i2c
2025-11-10 Update PCB to connect 4th right column
2025-11-10 Implement keyboard scanning
2025-11-10 Add keyboard pin defs
2025-11-10 Fix i2c frequency
2025-11-10 Implement the keyboard scanning logic
2025-11-14 Soft link right hand to primary copy
2025-11-14 Label parts for JLCPCB
2025-11-14 Adjust left hand silkscreen; holes
2025-11-14 Generate left_hand v0.4 for assembly
2025-11-14 Add DNP for right hand
2025-11-15 Adjust right hand mounts, testpoints
2025-11-15 Relabel right hand
2025-11-15 Shrink one problem hole
2025-11-15 Mark misc do not populate
2025-11-16 Prep for assembly ordering
2025-11-16 Create keycap print files
2025-11-16 Create variant for jlcpcb cost golf
2025-11-16 Label LCSC
2025-11-16 Create right hand order for JLCPCB
2025-11-19 Switch test points
2025-11-19 Add charge level check and more logs
2025-11-19 Set default info on release
2025-11-19 Rework and flesh out keyboard scanning
2025-11-19 Add libudev dependency
2025-11-24 Increase plover gemini PR baud rate
2025-11-24 Add translation pin enable trigger
2025-11-24 Consolidate Rust dependencies
2025-11-24 Add pin event time checks
2026-01-20 Implement base USB commns; fix timestamps
2026-01-20 Fix pin logic
2026-01-20 Add trace messages for clock tick
2026-01-20 Even more debug tweaking
2026-01-21 Try setting input and output line request flags
2026-01-22 Enhance panic prints to log
2026-01-25 Add more debug to battery_control initialization
2026-01-25 Update STEP files
2026-01-25 Update assembly files
2026-01-25 Add plover plugin skeleton
2026-01-25 Add more trace
2026-01-25 Update build scripts
2026-01-25 Update poky
2026-01-25 Temporarily disable rust services
2026-01-25 Remove duplicate translation pin service
2026-01-25 Temporarily remove user data partition
2026-01-25 Set line request flags back to just open drain
2026-01-25 Add features to bare_err_tree
2026-01-25 Use libgpiod-tools for debug
2026-01-25 Try output and input args
2026-02-15 Rework I2C and battery monitor
2026-02-15 Various debug tweaks
2026-02-16 Battery monitor chem ID u16
2026-02-16 Set I2C back to max speed
2026-02-16 Clock when SDA is stuck
2026-02-16 Avoid crashes before charging is enabled
2026-02-16 Charging fixes
2026-02-17 Add microsd flip flex PCB
2026-02-20 Create stencil for microsd flipper
2026-06-07 Misc PCB changes
2026-06-07 Add hacked together stand

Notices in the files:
left_hand.kicad_sch:
NO WARRANTY. See license.
https://creativecommons.org/licenses/by-sa/4.0
© 2025. This work is openly licensed via CC BY-SA 4.0.
